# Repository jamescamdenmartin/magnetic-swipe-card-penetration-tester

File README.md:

Magnetic Swipe Card Penetration Testor

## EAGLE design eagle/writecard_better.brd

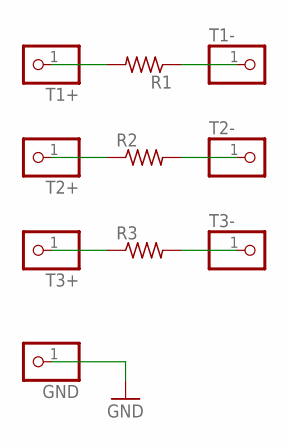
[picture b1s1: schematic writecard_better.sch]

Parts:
GND: PINHD-1X1; 1X01
R1, R2, R3: R-US_R1206; R1206
T1+, T1-, T2+, T2-, T3+, T3-: PINHD-1X1; 1X01

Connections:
GND: GND.1
unnamed: R1.1, T1-.1
unnamed: R1.2, T1+.1
unnamed: R3.1, T3+.1
unnamed: R2.1, T2+.1
unnamed: R2.2, T2-.1
unnamed: R3.2, T3-.1

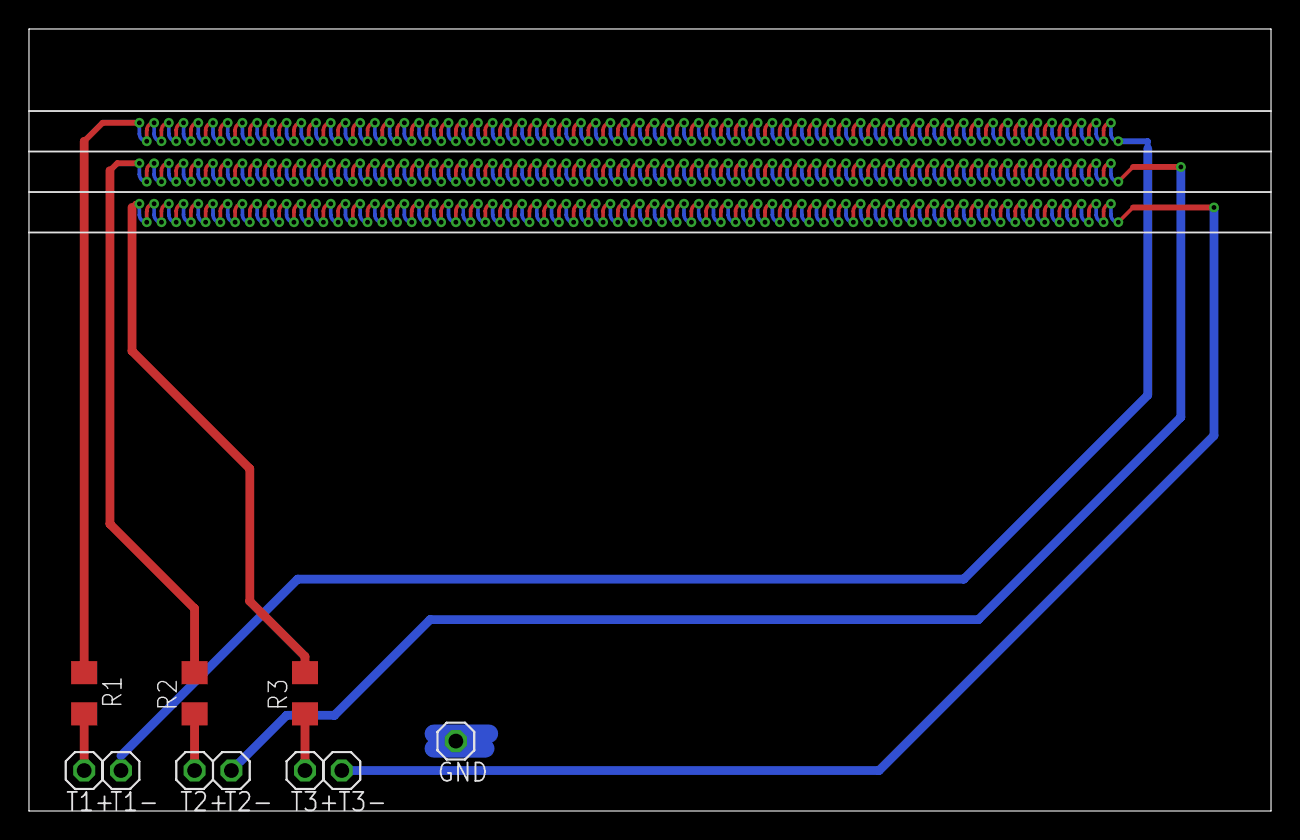
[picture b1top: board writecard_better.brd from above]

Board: 2 copper layers, 85.7 x 54.0 mm, 10 parts (0 on the bottom side), 6 nets.

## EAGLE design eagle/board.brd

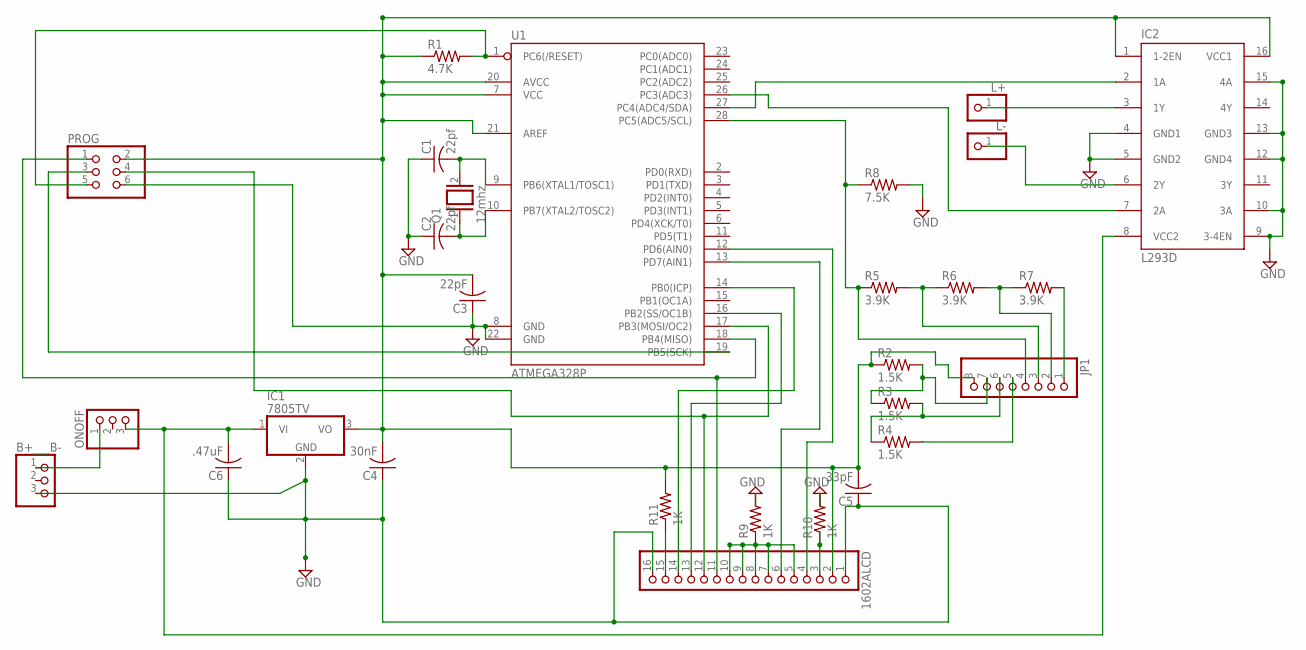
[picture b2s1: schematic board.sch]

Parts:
1602ALCD: PINHD-1X16; 1X16
B+___B-: PINHD-1X3; 1X03
C1, C2: 22pf; C050-024X044
C3: 22pF; C025-025X050
C4: 30nF; C025-025X050
C5: 33pF; C025-025X050
C6: .47uF; C025-025X050
IC1: 7805TV; TO220V
IC2: L293D; DIL16
JP1: PINHD-1X8; 1X08
L+: PINHD-1X1; 1X01
L-: PINHD-1X1; 1X01
ONOFF: PINHD-1X3; 1X03
PROG: PINHD-2X3; 2X03
Q1: 12mhz; QS
R1: 4.7K; 0207/7
R2, R3, R4: 1.5K; 0207/7
R5, R6, R7: 3.9K; 0207/7
R8: 7.5K; 0207/7
R9, R10, R11: 1K; 0207/7
U1: ATMEGA328P; DIL28-3

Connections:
GND: 1602ALCD.1, 1602ALCD.16, B+___B-.3, C1.1, C2.1, C3.1, C4.1, C5.1, C6.1, IC1.2 (GND), IC2.4 (GND1), IC2.5 (GND2), IC2.9 (3-4EN), IC2.10 (3A), IC2.12 (GND4), IC2.13 (GND3), IC2.15 (4A), PROG.6, R8.2, R9.2, R10.2, U1.8 (GND), U1.22 (GND)
unnamed: 1602ALCD.2, C3.2, C4.2, C5.2, IC1.3 (VO), IC2.1 (1-2EN), IC2.16 (VCC1), JP1.8, PROG.2, R1.1, R2.1, R11.2, U1.7 (VCC), U1.20 (AVCC), U1.21 (AREF)
unnamed: B+___B-.1, ONOFF.1
unnamed: C6.2, IC1.1 (VI), IC2.8 (VCC2), ONOFF.3
unnamed: C2.2, Q1.1, U1.10 (PB7(XTAL2/TOSC2))
unnamed: C1.2, Q1.2, U1.9 (PB6(XTAL1/TOSC1))
unnamed: PROG.5, R1.2, U1.1 (PC6(/RESET))
unnamed: JP1.4, R5.1, R8.1, U1.28 (PC5(ADC5/SCL))
unnamed: JP1.3, R5.2, R6.1
unnamed: JP1.2, R6.2, R7.1
unnamed: JP1.1, R7.2
unnamed: IC2.7 (2A), U1.26 (PC3(ADC3))
unnamed: JP1.5, R4.2
unnamed: JP1.6, R3.2, R4.1
unnamed: JP1.7, R2.2, R3.1
unnamed: 1602ALCD.14, U1.14 (PB0(ICP))
unnamed: 1602ALCD.13, U1.16 (PB2(SS/OC1B))
unnamed: IC2.2 (1A), U1.27 (PC4(ADC4/SDA))
unnamed: 1602ALCD.11, PROG.1, U1.18 (PB4(MISO))
unnamed: 1602ALCD.5, 1602ALCD.7, 1602ALCD.8, 1602ALCD.9, 1602ALCD.10, R9.1
unnamed: 1602ALCD.6, U1.13 (PD7(AIN1))
unnamed: 1602ALCD.3, R10.1
unnamed: 1602ALCD.4, U1.12 (PD6(AIN0))
unnamed: PROG.3, U1.19 (PB5(SCK))
unnamed: 1602ALCD.15, R11.1
unnamed: 1602ALCD.12, PROG.4, U1.17 (PB3(MOSI/OC2))
unnamed: IC2.3 (1Y), L+.1
unnamed: IC2.6 (2Y), L-.1

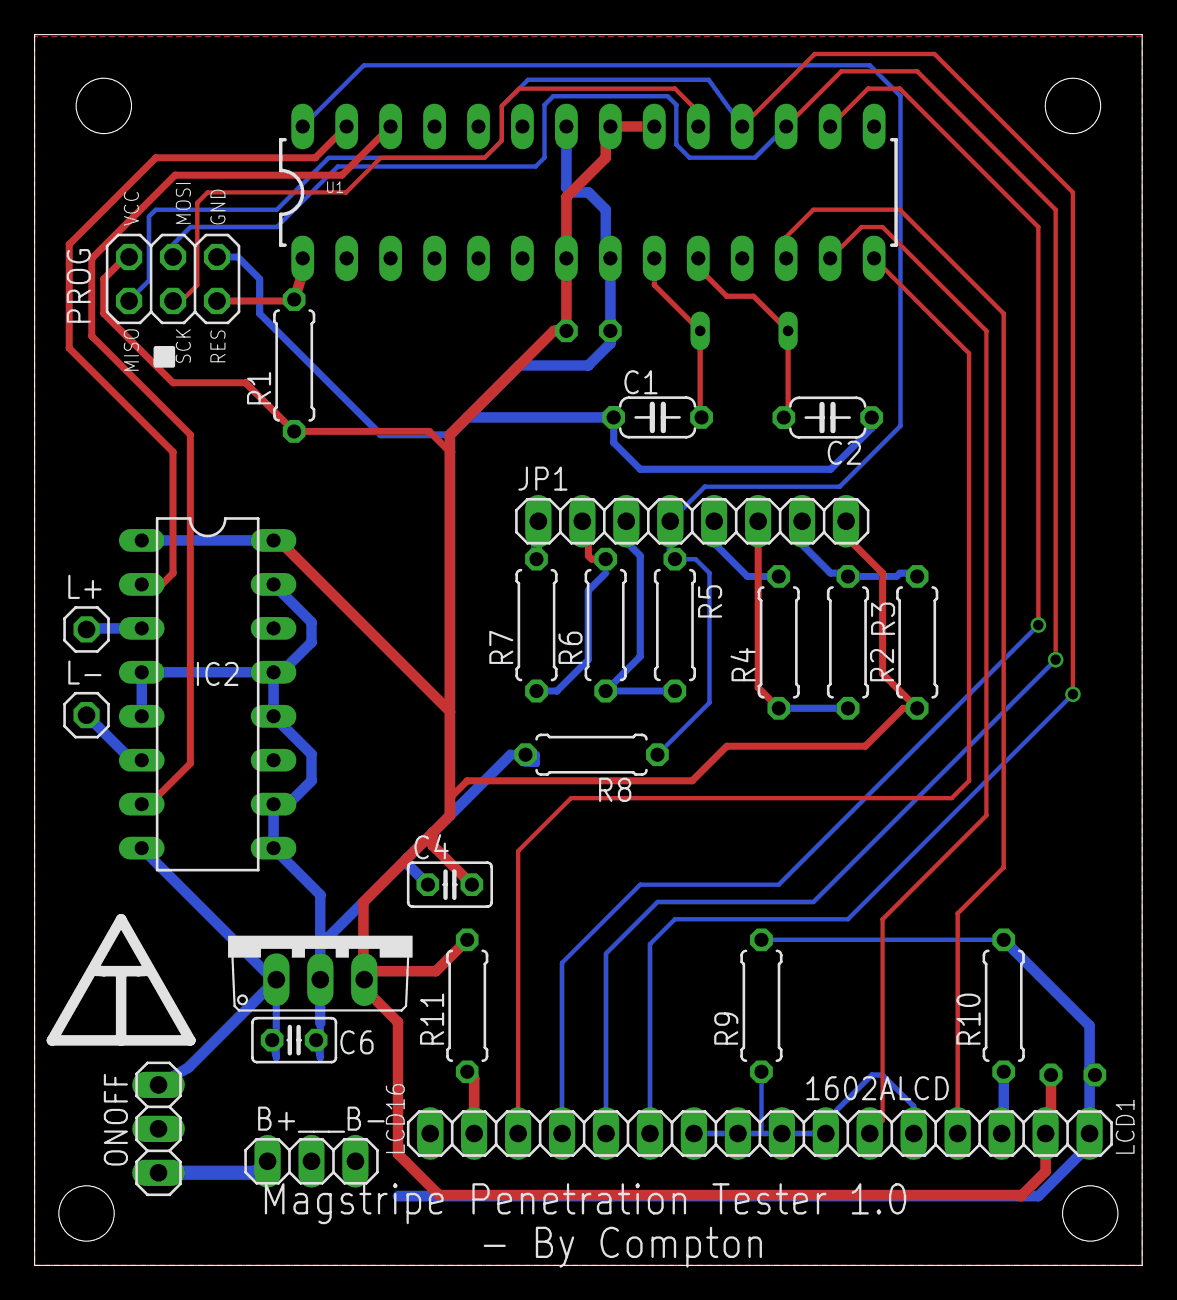
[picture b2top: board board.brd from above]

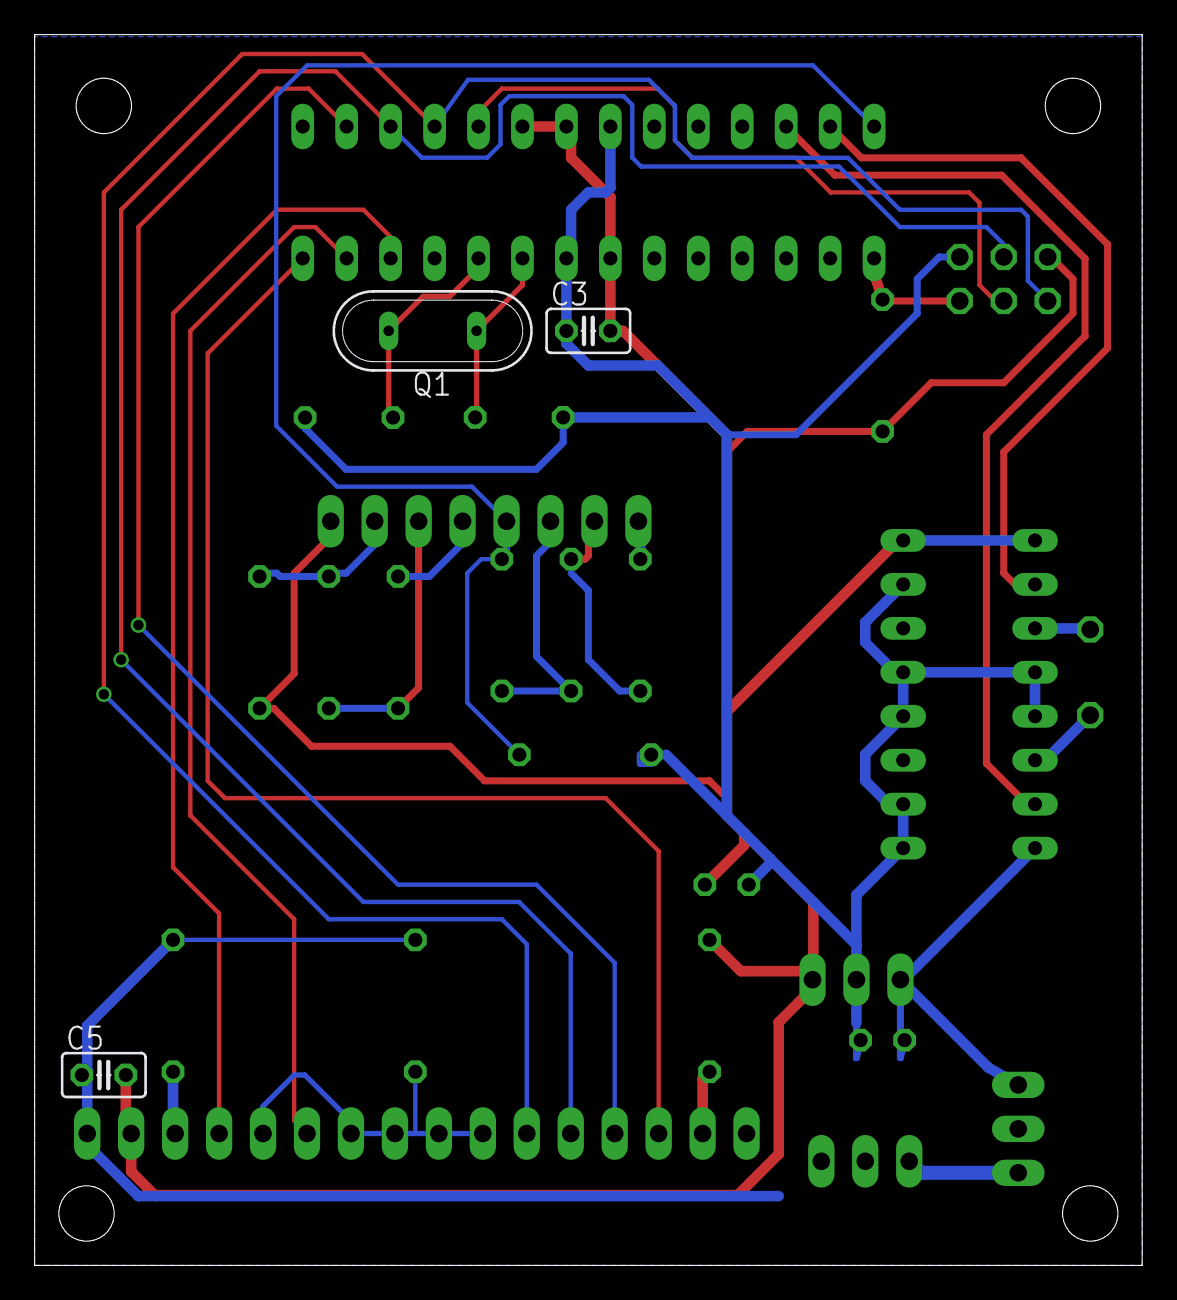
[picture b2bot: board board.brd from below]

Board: 2 copper layers, 64.0 x 71.1 mm, 28 parts (3 on the bottom side), 28 nets.

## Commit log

2015-06-20 v.09 Initial Commit
2015-06-20 Fix heading information
2015-06-20 Fixed circuit diagram export
2015-07-10 Refactored code into more modules.
2015-07-10 Updated .gitignore
2015-07-10 Added code for saving card data to EEPROM
2015-07-11 Implemented the saved code selection shortcut menu
2015-07-13 Ported code to ATMEGA328 and changed build parameters to lower program flash usage.
2015-07-13 Datatype optimizations
2016-01-01 Converted code to run on the Atmega328P
2016-01-01 Eagle Files
2016-01-01 Working saved data menu, output, editor
2016-01-01 Change code input to take advantage of a larger keypad.
2016-01-01 Update git ignore
2018-01-23 Prettify code
2018-01-23 Credit card shaped write head for 0.8mm thick, 2oz copper, Elecrow PCB

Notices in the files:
parts and their libraries:
SparkFun-DigitalIC: Licensing: Creative Commons ShareAlike 4.0 International - https://creativecommons.org/licenses/by-sa/4.0
